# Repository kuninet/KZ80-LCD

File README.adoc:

= LCD SC1603 BOARD for KZ80マイコン 

== 概要
* 16桁x2行のLCDモジュール SC1602をSBC8080バス(KZ80-CPUBとか)へ接続するボードです。

== 説明
* SBC8080バス(KZ80-CPUBとか)へ接続するボードです。
* 74HC138でI/Oアドレスデコードします。$80〜や$90〜に設定がおすすめ。

== I/Oアドレス($90〜の場合)
* I/Oアドレスを$90〜とした場合

|===
|I/Oアドレス|RD/WR|説明

|$90
|WR
|各種設定

|$91
|WR
|CG RAM、DDRAMへデータ書き込み

|$92
|RD
|Busyフラグ、CG RAM、DDRAMアドレス読み出し

|$93
|RD
|CG RAM、DDRAMからデータ読み出し

|===

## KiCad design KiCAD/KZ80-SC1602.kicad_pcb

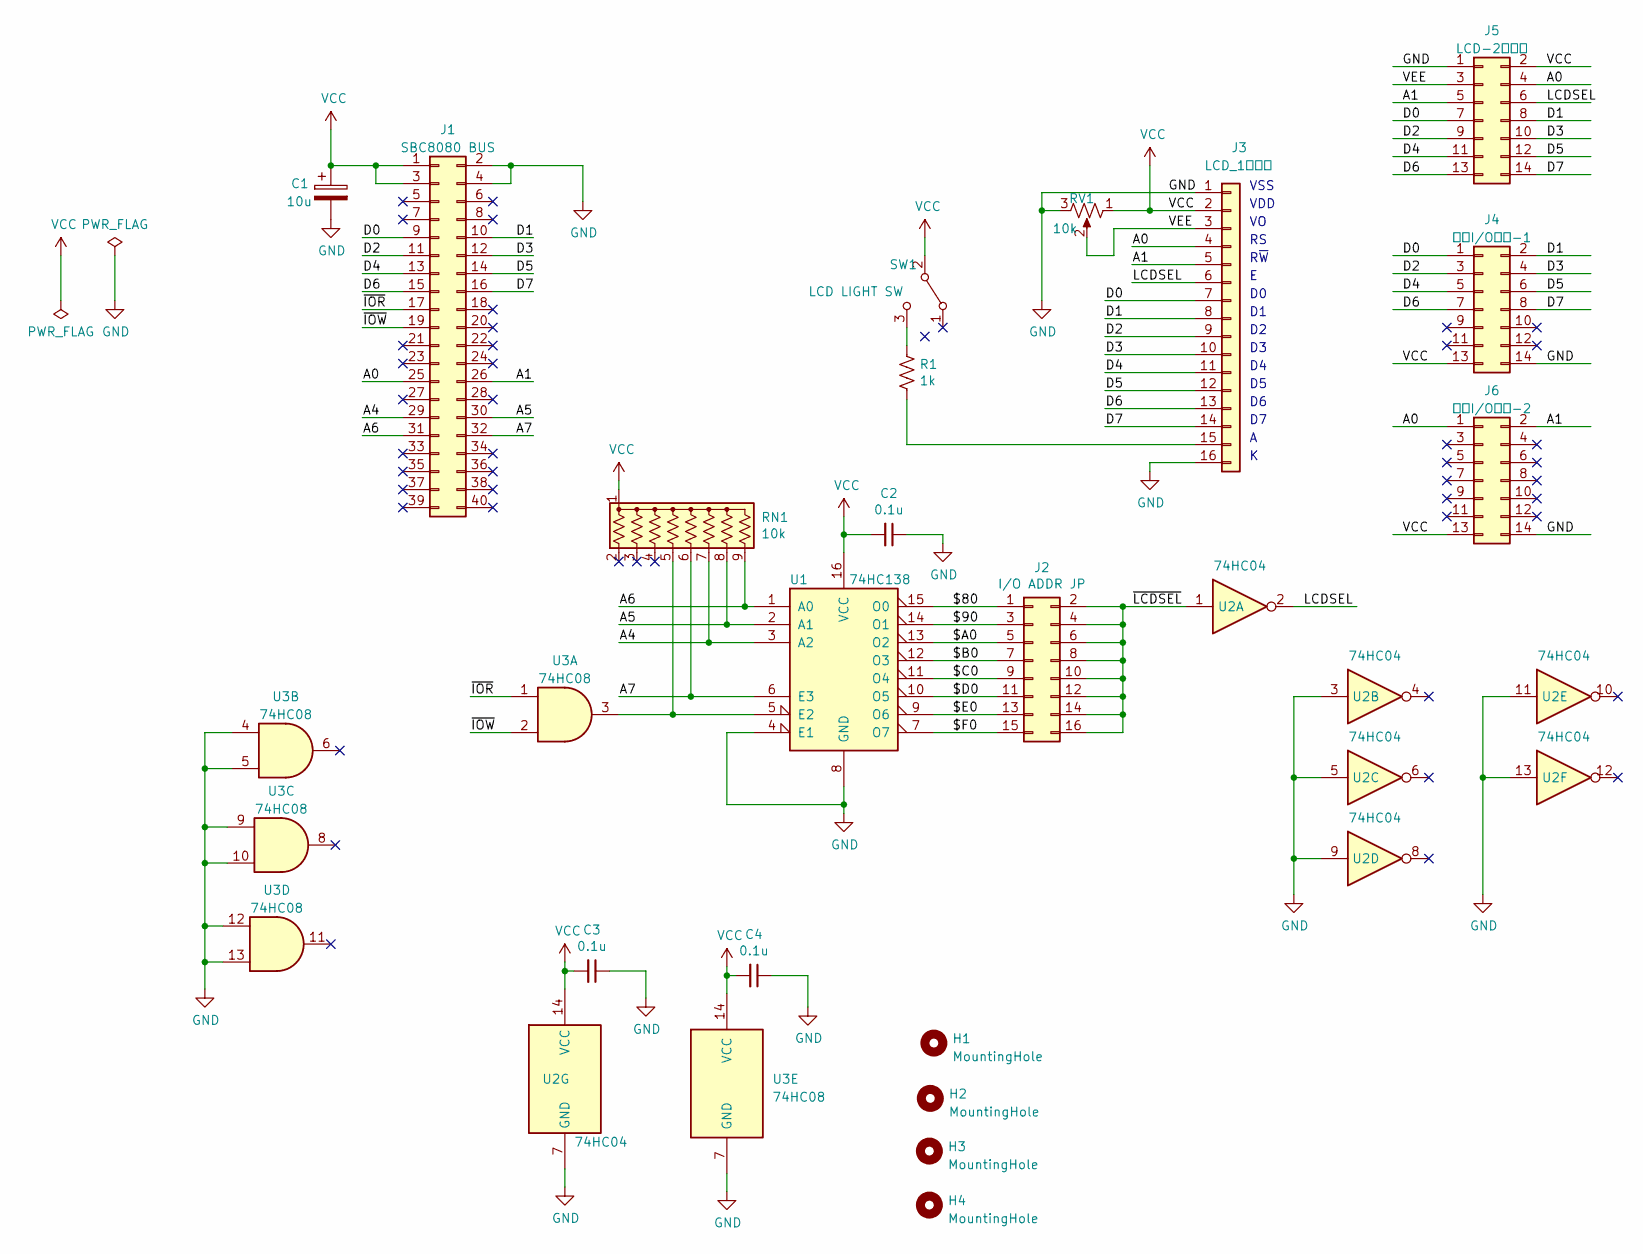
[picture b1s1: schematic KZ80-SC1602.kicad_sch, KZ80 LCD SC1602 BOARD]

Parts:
C1: 10u; CP_Radial_D5.0mm_P2.50mm
C2, C3, C4: 0.1u; C_Disc_D3.0mm_W1.6mm_P2.50mm
H1, H2, H3, H4: MountingHole; MountingHole_3.2mm_M3
J1: SBC8080 BUS; PinHeader_2x20_P2.54mm_Horizontal
J2: I/O ADDR JP; PinHeader_2x08_P2.54mm_Vertical
J3: LCD_1列端子; PinHeader_1x16_P2.54mm_Vertical
J4: 外部I/O端子-1; PinHeader_2x07_P2.54mm_Vertical
J5: LCD-2列端子; PinHeader_2x07_P2.54mm_Vertical
J6: 外部I/O端子-2; PinHeader_2x07_P2.54mm_Vertical
R1: 1k; R_Axial_DIN0207_L6.3mm_D2.5mm_P10.16mm_Horizontal
RN1: 10k; R_Array_SIP9
RV1: 10k; Potentiometer_Vishay_T73YP_Vertical
SW1: LCD LIGHT SW; PinHeader_1x03_P2.54mm_Vertical
U1: 74HC138; DIP-16_W7.62mm_Socket
U2: 74HC04; DIP-14_W7.62mm_Socket
U3: 74HC08; DIP-14_W7.62mm_Socket

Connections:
/$80: J2.1, U1.15 (O0)
/$90: J2.3, U1.14 (O1)
/$A0: J2.5, U1.13 (O2)
/$B0: J2.7, U1.12 (O3)
/$C0: J2.9, U1.11 (O4)
/$D0: J2.11, U1.10 (O5)
/$E0: J2.13, U1.9 (O6)
/$F0: J2.15, U1.7 (O7)
/A0: J1.25, J3.4, J5.4, J6.1
/A1: J1.26, J3.5, J5.5, J6.2
/A4: J1.29, RN1.7 (R6), U1.3 (A2)
/A5: J1.30, RN1.8 (R7), U1.2 (A1)
/A6: J1.31, RN1.9 (R8), U1.1 (A0)
/A7: J1.32, RN1.6 (R5), U1.6 (E3)
/D0: J1.9, J3.7, J4.1, J5.7
/D1: J1.10, J3.8, J4.2, J5.8
/D2: J1.11, J3.9, J4.3, J5.9
/D3: J1.12, J3.10, J4.4, J5.10
/D4: J1.13, J3.11, J4.5, J5.11
/D5: J1.14, J3.12, J4.6, J5.12
/D6: J1.15, J3.13, J4.7, J5.13
/D7: J1.16, J3.14, J4.8, J5.14
/LCDSEL: J3.6, J5.6, U2.2
/VEE: J3.3, J5.3, RV1.2
/~IOR: J1.17, U3.1
/~IOW: J1.19, U3.2
/~LCDSEL: J2.2, J2.4, J2.6, J2.8, J2.10, J2.12, J2.14, J2.16, U2.1
GND: C1.2, C2.1, C3.1, C4.1, J1.2, J1.4, J3.1, J3.16, J4.14, J5.1, J6.14, RV1.3, U1.4 (E1), U1.8 (GND), U2.3, U2.5, U2.7 (GND), U2.9, U2.11, U2.13, U3.4, U3.5, U3.7 (GND), U3.9, U3.10, U3.12, U3.13
unnamed: J3.15, R1.2
unnamed: RN1.5 (R4), U1.5 (E2), U3.3
unnamed: R1.1, SW1.3 (C)
VCC: C1.1, C2.2, C3.2, C4.2, J1.1, J1.3, J3.2, J4.13, J5.2, J6.13, RN1.1 (common), RV1.1, SW1.2 (B), U1.16 (VCC), U2.14 (VCC), U3.14 (VCC)

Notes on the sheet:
VSS
VDD
R~{W}

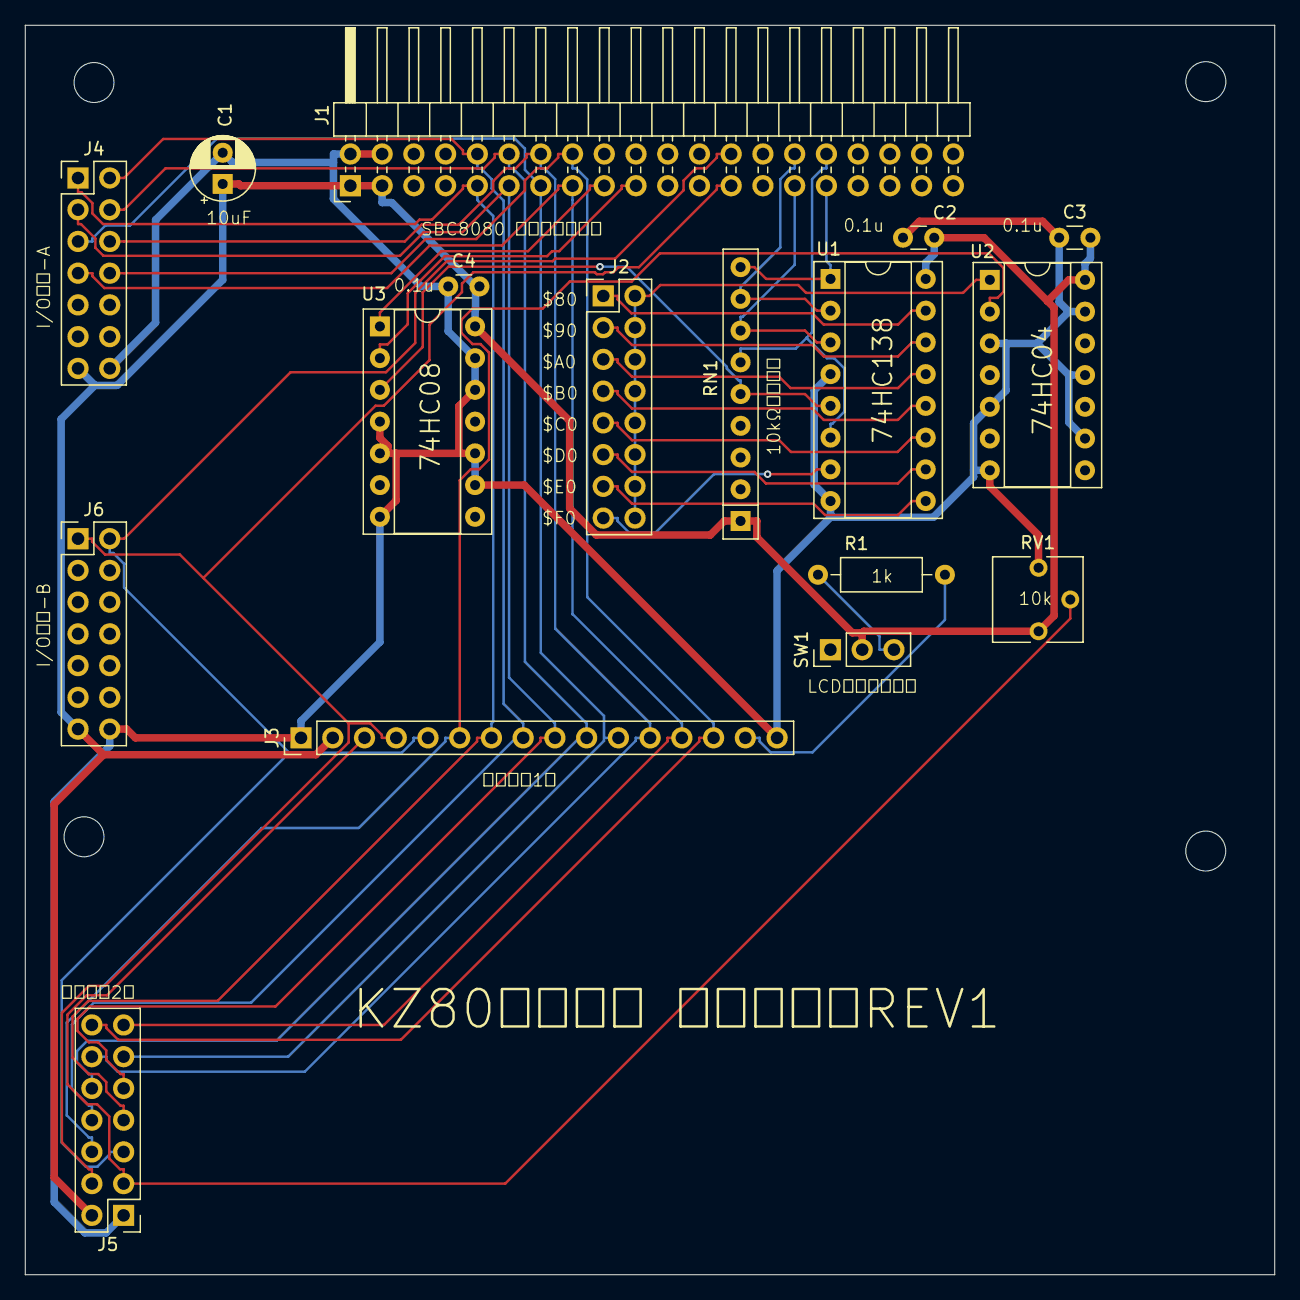
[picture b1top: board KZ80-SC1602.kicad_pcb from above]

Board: 2 copper layers, 100.0 x 100.0 mm, 21 parts (0 on the bottom side), 32 nets.

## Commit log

2023-03-24 REV1基板ガーバーデータ出力
2023-04-08 LCD表示テストプログラム追加
